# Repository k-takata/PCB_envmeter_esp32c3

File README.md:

# IoT環境メーター / スマートリモコン

## 概要

ESP32-C3とBoschのBME680を使い、温度、湿度、気圧、二酸化炭素換算値などを測定し、結果を[Ambient](https://ambidata.io/)にアップロードできる環境メーターです。  
表示には0.96inch OLEDを使用し、スイッチで通常表示・詳細表示・簡易表示を切り替えることができます。  
Rev. 2 からは赤外線送受信部を備え、スマートリモコン機能も使うことができます。

Rev. 1 のソフトウェア及び解説記事は「[ESP32-C3とBME680でIoT環境メーターを作る](https://zenn.dev/k_takata/articles/esp32c3-envmeter)」で公開しています。  
Rev. 2 のソフトウェア及び解説記事は以下で公開しています。

* [ESP32-C3とBME680でIoT環境メーター/スマートリモコンを作る (その1)](https://zenn.dev/k_takata/articles/esp32c3-envmeter-rev2-1)
* [ESP32-C3とBME680でIoT環境メーター/スマートリモコンを作る (その2)](https://zenn.dev/k_takata/articles/esp32c3-envmeter-rev2-2)

## 使用したソフトウェア

KiCad 7.0

## 回路図

## 基板パターン図

## 部品表

### IoT環境メーター部分

| Reference           |個数|値    | 説明 |
|---------------------|----|------|------|
|C1                   |   1|100μF|電解コンデンサー φ6.3[^1] (100 ~ 470μF)|
|C2                   |   1|  1μF|[積層セラミックコンデンサー](https://akizukidenshi.com/catalog/g/g115940/)、2.54mmピッチ|
|C3 (\*1)             |   1| 10μF|積層セラミックコンデンサー、表面実装 (3225 あるいは 3216 サイズ)|
|C4 (\*1)             |   1| 10μF|[積層セラミックコンデンサー](https://akizukidenshi.com/catalog/g/g103095/)、5mmピッチ|
|D1                   |   1|      |赤色LED φ5|
|F1 (\*2)             |   1|  0.5A|[ポリヒューズ](https://akizukidenshi.com/catalog/g/g115300/)、表面実装|
|F2 (\*2)             |   1|  1.1A|[ポリヒューズ](https://akizukidenshi.com/catalog/g/g100507/)|
|J1 (\*3)             |   1|[5077CR-16-SMC2-BK-TR](https://akizukidenshi.com/catalog/g/g114356/)|USB Type-Cコネクター|
|J2 (\*3)             |   1|      |[USB Type-CコネクターDIP化キット](https://akizukidenshi.com/catalog/g/g115426/)、[同等品](https://akizukidenshi.com/catalog/g/g113080/)でも可|
|J3                   |   1|      |[細ピンソケット](https://akizukidenshi.com/catalog/g/g110073/) 1x4 (あるいは[1列ICソケット](https://akizukidenshi.com/catalog/g/g103470/))|
|J4                   |   1|      |[ピンソケット](https://akizukidenshi.com/catalog/g/g105779/) 1x4 (あるいは[ロープロファイルピンソケット](https://akizukidenshi.com/catalog/g/g100661/))|
|(J3)                 |   1|[AE-BME680](https://akizukidenshi.com/catalog/g/g114469/)|総合環境センサー|
|(J4)                 |   1|      |[0.96インチ 128×64ドット OLED](https://akizukidenshi.com/catalog/g/g112031/)、SSD1306搭載|
|R1, R2               |   2|5.1kΩ|緑茶赤金、小型|
|R3, R4, R5, R6       |   4| 10kΩ|茶黒橙金|
|SW1                  |   1|Reset |[タクトスイッチ(赤)](https://akizukidenshi.com/catalog/g/g103646/)|
|SW2                  |   1|Mode  |[タクトスイッチ(黒)](https://akizukidenshi.com/catalog/g/g103647/)|
|U1                   |   1|[ESP32-C3-WROOM-02-N4](https://akizukidenshi.com/catalog/g/g117493/)|Wi-Fi モジュール|
|U2 (\*4)             |   1|[AP7333-33SAG](https://akizukidenshi.com/catalog/g/g111360/)|低損失三端子レギュレーター 3.3V 300mA|
|U3 (\*4)             |   1|[NJM2845DL1-33](https://akizukidenshi.com/catalog/g/g111299/)|低損失三端子レギュレーター 3.3V 800mA|

[^1]: このサイズならば、まっすぐ足が奥まで挿せる。

注:
* (\*1) C3, C4はどちらかを選択します。基板上にはC3の表示のみあります。表面実装の半田付けが難しい場合はC4を選択してください。
* (\*2) F1, F2はどちらかを選択します。基板上にはF1の表示のみあります。F1がお勧めですが、表面実装の半田付けが難しい場合はF2でも可です。
* (\*3) J1, J2はどちらかを選択します。基板上にはJ1の表示のみあります。表面実装の半田付けが難しい場合はJ2を選択してください。
* (\*4) U2, U3はどちらかを選択します。U2の方が安価ですが300mAしか使えないため、Wi-Fiをフルパワーで使いたい場合は、U3の方がお勧めです。
* AE-BME680を取り外す予定がなければ、ピンソケット(J3)を使わず直接接続してもかまいません。
* OLEDを取り外す予定がなければ、ピンソケット(J4)を使わず直接接続してもかまいません。

### 赤外線受信部

| Reference           |個数|値    | 説明 |
|---------------------|----|------|------|
|U4                   |   1|[OSRB38C9AA](https://akizukidenshi.com/catalog/g/g104659/)|赤外線リモコン受信モジュール|

注: 赤外線リモコン受信機能を使わない場合は組み立て不要です。

### 赤外線送信部

| Reference           |個数|値    | 説明 |
|---------------------|----|------|------|
|D2                   |   1|[OSI5LA5113A](https://akizukidenshi.com/catalog/g/g112612/)|赤外線LED φ5|
|Q1                   |   1|[2SC2001](https://akizukidenshi.com/catalog/g/g113828/)||
|R7                   |   1| 680Ω|青灰茶金|
|R8                   |   1|4.7kΩ|黄紫赤金|
|R9                   |   1| 5.1Ω|緑茶金金、1/2W 小型|

注: 赤外線リモコン送信機能を使わない場合は組み立て不要です。

## 使い方

### Rev. 1

「[ESP32-C3とBME680でIoT環境メーターを作る](https://zenn.dev/k_takata/articles/esp32c3-envmeter)」を参照してください。

### Rev. 2

以下の記事を参照してください。

* [ESP32-C3とBME680でIoT環境メーター/スマートリモコンを作る (その1)](https://zenn.dev/k_takata/articles/esp32c3-envmeter-rev2-1)
* [ESP32-C3とBME680でIoT環境メーター/スマートリモコンを作る (その2)](https://zenn.dev/k_takata/articles/esp32c3-envmeter-rev2-2)

## 完成品

### Rev. 1

通常表示<br>

詳細表示<br>

簡易表示<br>

### Rev. 2

## License

CC0

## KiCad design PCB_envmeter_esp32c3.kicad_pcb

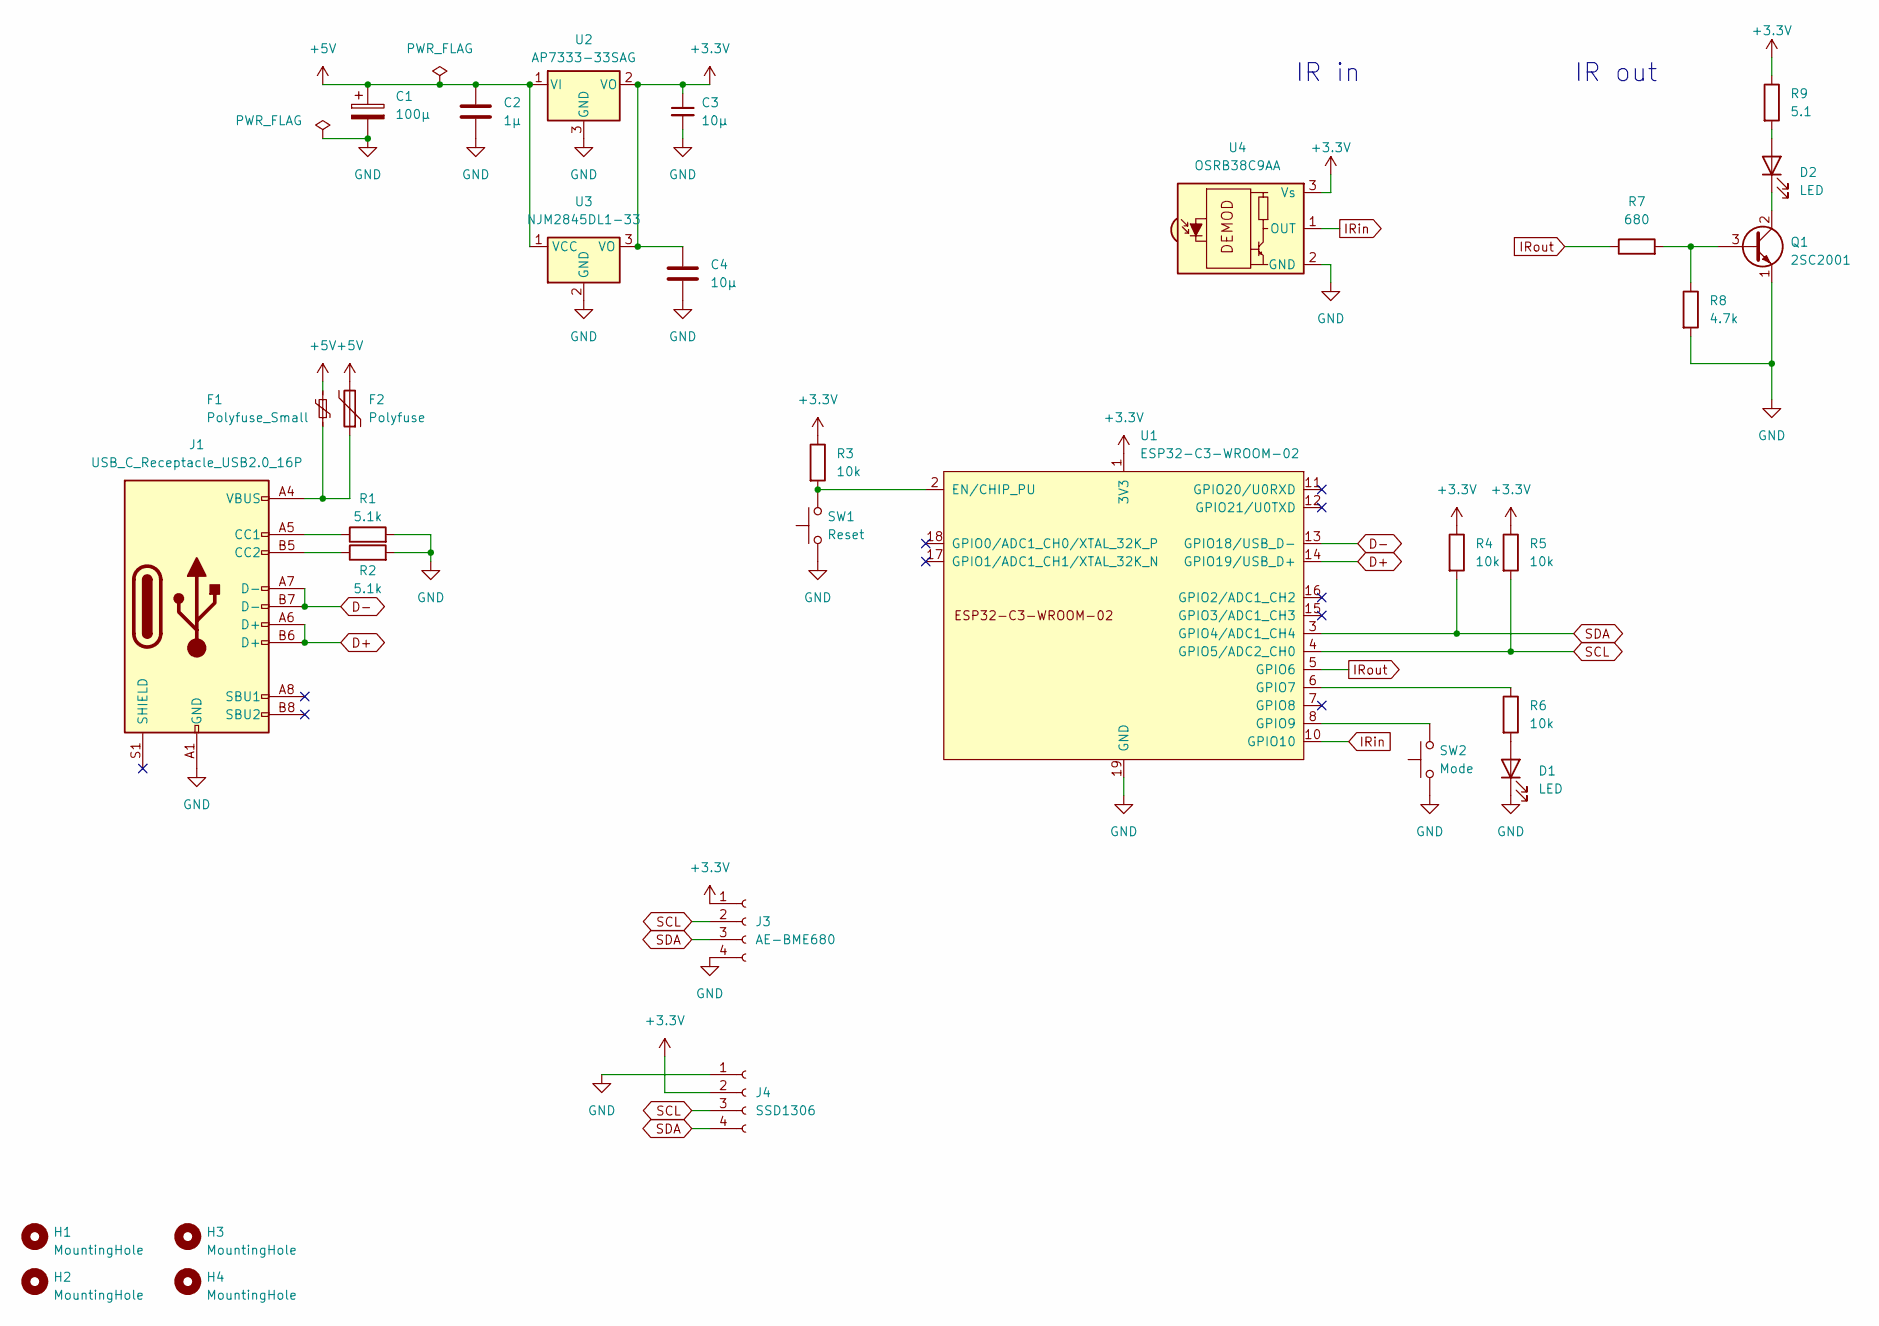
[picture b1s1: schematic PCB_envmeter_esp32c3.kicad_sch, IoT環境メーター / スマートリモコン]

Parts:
C1: 100μ; CP_Radial_D6.3mm_P2.50mm
C2: 1μ; C_Disc_D3.8mm_W2.6mm_P2.50mm
C3: 10μ; C_1210_3225Metric_Pad1.33x2.70mm_HandSolder
C4: 10μ; C_Disc_D4.7mm_W2.5mm_P5.00mm
D1: LED; LED_D5.0mm
D2: LED; LED_D5.0mm_IRGrey
F1: Polyfuse_Small; Fuse_1206_3216Metric_Pad1.42x1.75mm_HandSolder
F2: Polyfuse; C_Disc_D4.3mm_W1.9mm_P5.00mm
H1, H2, H3, H4: MountingHole; MountingHole_3.2mm_M3
J1: USB_C_Receptacle_USB2.0_16P; Connector_USB_C_simple_combo
J3: AE-BME680; PinSocket_1x04_P2.54mm_Vertical
J4: SSD1306; PinSocket_1x04_P2.54mm_Vertical
Q1: 2SC2001; TO-92_Inline_Wide
R1, R2: 5.1k; R_Axial_DIN0204_L3.6mm_D1.6mm_P5.08mm_Horizontal
R3, R4, R5, R6: 10k; R_Axial_DIN0207_L6.3mm_D2.5mm_P7.62mm_Horizontal
R7: 680; R_Axial_DIN0207_L6.3mm_D2.5mm_P7.62mm_Horizontal
R8: 4.7k; R_Axial_DIN0207_L6.3mm_D2.5mm_P7.62mm_Horizontal
R9: 5.1; R_Axial_DIN0207_L6.3mm_D2.5mm_P7.62mm_Horizontal
SW1: Reset; SW_PUSH_6mm
SW2: Mode; SW_PUSH_6mm
U1: ESP32-C3-WROOM-02
U2: AP7333-33SAG; SOT-23
U3: NJM2845DL1-33; TO-252-2
U4: OSRB38C9AA; Vishay_MOLD-3Pin

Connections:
+3.3V: C3.1, C4.1, J3.1, J4.2, R3.1, R4.1, R5.1, R9.1, U1.1 (3V3), U2.2 (VO), U3.3 (VO), U4.3 (Vs)
+5V: C1.1, C2.1, F1.2, F2.2, U2.1 (VI), U3.1 (VCC)
D+: J1.A6 (D+), J1.B6 (D+), U1.14 (GPIO19/USB_D+)
D-: J1.A7 (D-), J1.B7 (D-), U1.13 (GPIO18/USB_D-)
GND: C1.2, C2.2, C3.2, C4.2, D1.1 (K), J1.A1 (GND), J1.A12 (GND), J1.B1 (GND), J1.B12 (GND), J3.4, J4.1, Q1.1 (E), R1.2, R2.2, R8.2, SW1.1, SW2.1, U1.9 (GND), U1.19 (GND), U2.3 (GND), U3.2 (GND), U4.2 (GND)
IRin: U1.10 (GPIO10), U4.1 (OUT)
IRout: R7.1, U1.5 (GPIO6)
unnamed: D1.2 (A), R6.2
unnamed: D2.2 (A), R9.2
unnamed: D2.1 (K), Q1.2 (C)
unnamed: F1.1, F2.1, J1.A4 (VBUS), J1.A9 (VBUS), J1.B4 (VBUS), J1.B9 (VBUS)
unnamed: J1.A5 (CC1), R1.1
unnamed: J1.B5 (CC2), R2.1
unnamed: Q1.3 (B), R7.2, R8.1
unnamed: R3.2, SW1.2, U1.2 (EN/CHIP_PU)
unnamed: R6.1, U1.6 (GPIO7)
unnamed: SW2.2, U1.8 (GPIO9)
SCL: J3.2, J4.3, R5.2, U1.4 (GPIO5/ADC2_CH0)
SDA: J3.3, J4.4, R4.2, U1.3 (GPIO4/ADC1_CH4)

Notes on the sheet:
IR out
IR in

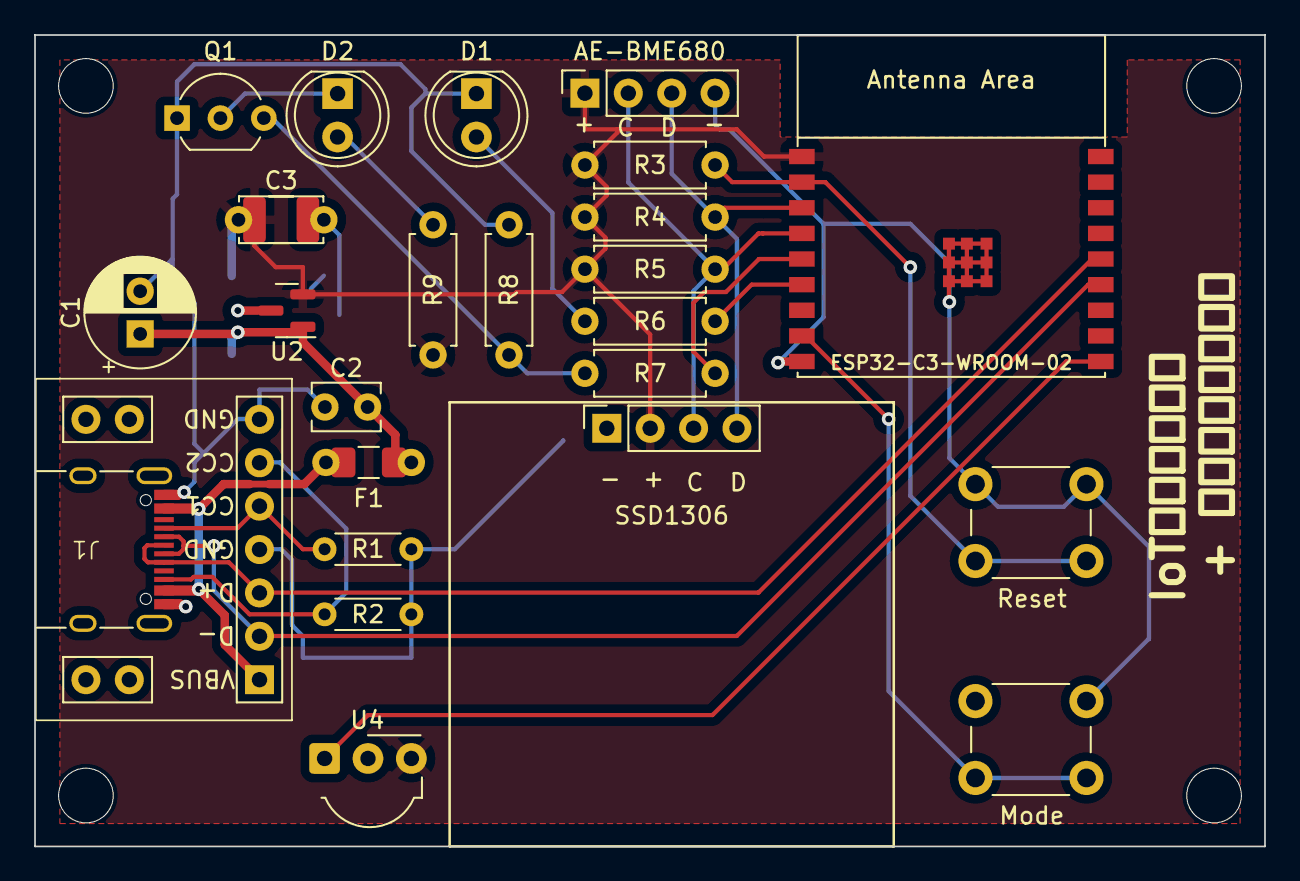
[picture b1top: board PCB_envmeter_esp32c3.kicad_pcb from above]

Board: 2 copper layers, 72.0 x 47.5 mm, 31 parts (1 on the bottom side), 19 nets.

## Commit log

2024-02-10 Update
    Values are changed after Garber files are generated.
2024-02-10 Add images
2024-02-10 Initial version
2024-02-10 Add README.md
2024-02-10 Add title
2024-02-10 Rename the project files
2024-02-10 Adjust schema layout
2024-02-11 doc: Change J3
    J3 を細ピンソケットに変更。
2024-02-17 Disconnect shield to GND
2024-02-17 Adjust capacitors position
2024-02-17 Revise wiring around USB connector
2024-02-17 Change footprint of SW1,2
2024-02-18 Change footprint
2024-02-24 完成品の写真を追加
2024-02-24 Add links
2024-02-25 Update parts list
2024-02-25 Update notes
2024-02-25 詳細表示の写真を追加
2024-02-25 Update F1 footprint
2024-02-28 Add simple mode photo
2024-03-01 Rev. 2
    * スマートリモコン機能追加
    - 赤外線送信部
    - 赤外線受信部
    * AE-BME680とSSD1306のパッド穴サイズを1.0mmから0.9mmに変更
    * JLCJLCJLCJLC を WayWayWay に変更
2024-03-01 Ignore pcbway_production
2024-03-01 Replace OSRB38C9AA symbol
2024-03-01 Renumber
2024-03-02 doc: Update for Rev. 2
2024-03-02 doc: Revise
2024-03-09 Add 3D model for USB connector
2024-03-14 doc: Update R9 description
2024-03-20 doc: Update about Rev. 2
2025-06-30 Update font name
2025-08-30 Adjust OLED position
